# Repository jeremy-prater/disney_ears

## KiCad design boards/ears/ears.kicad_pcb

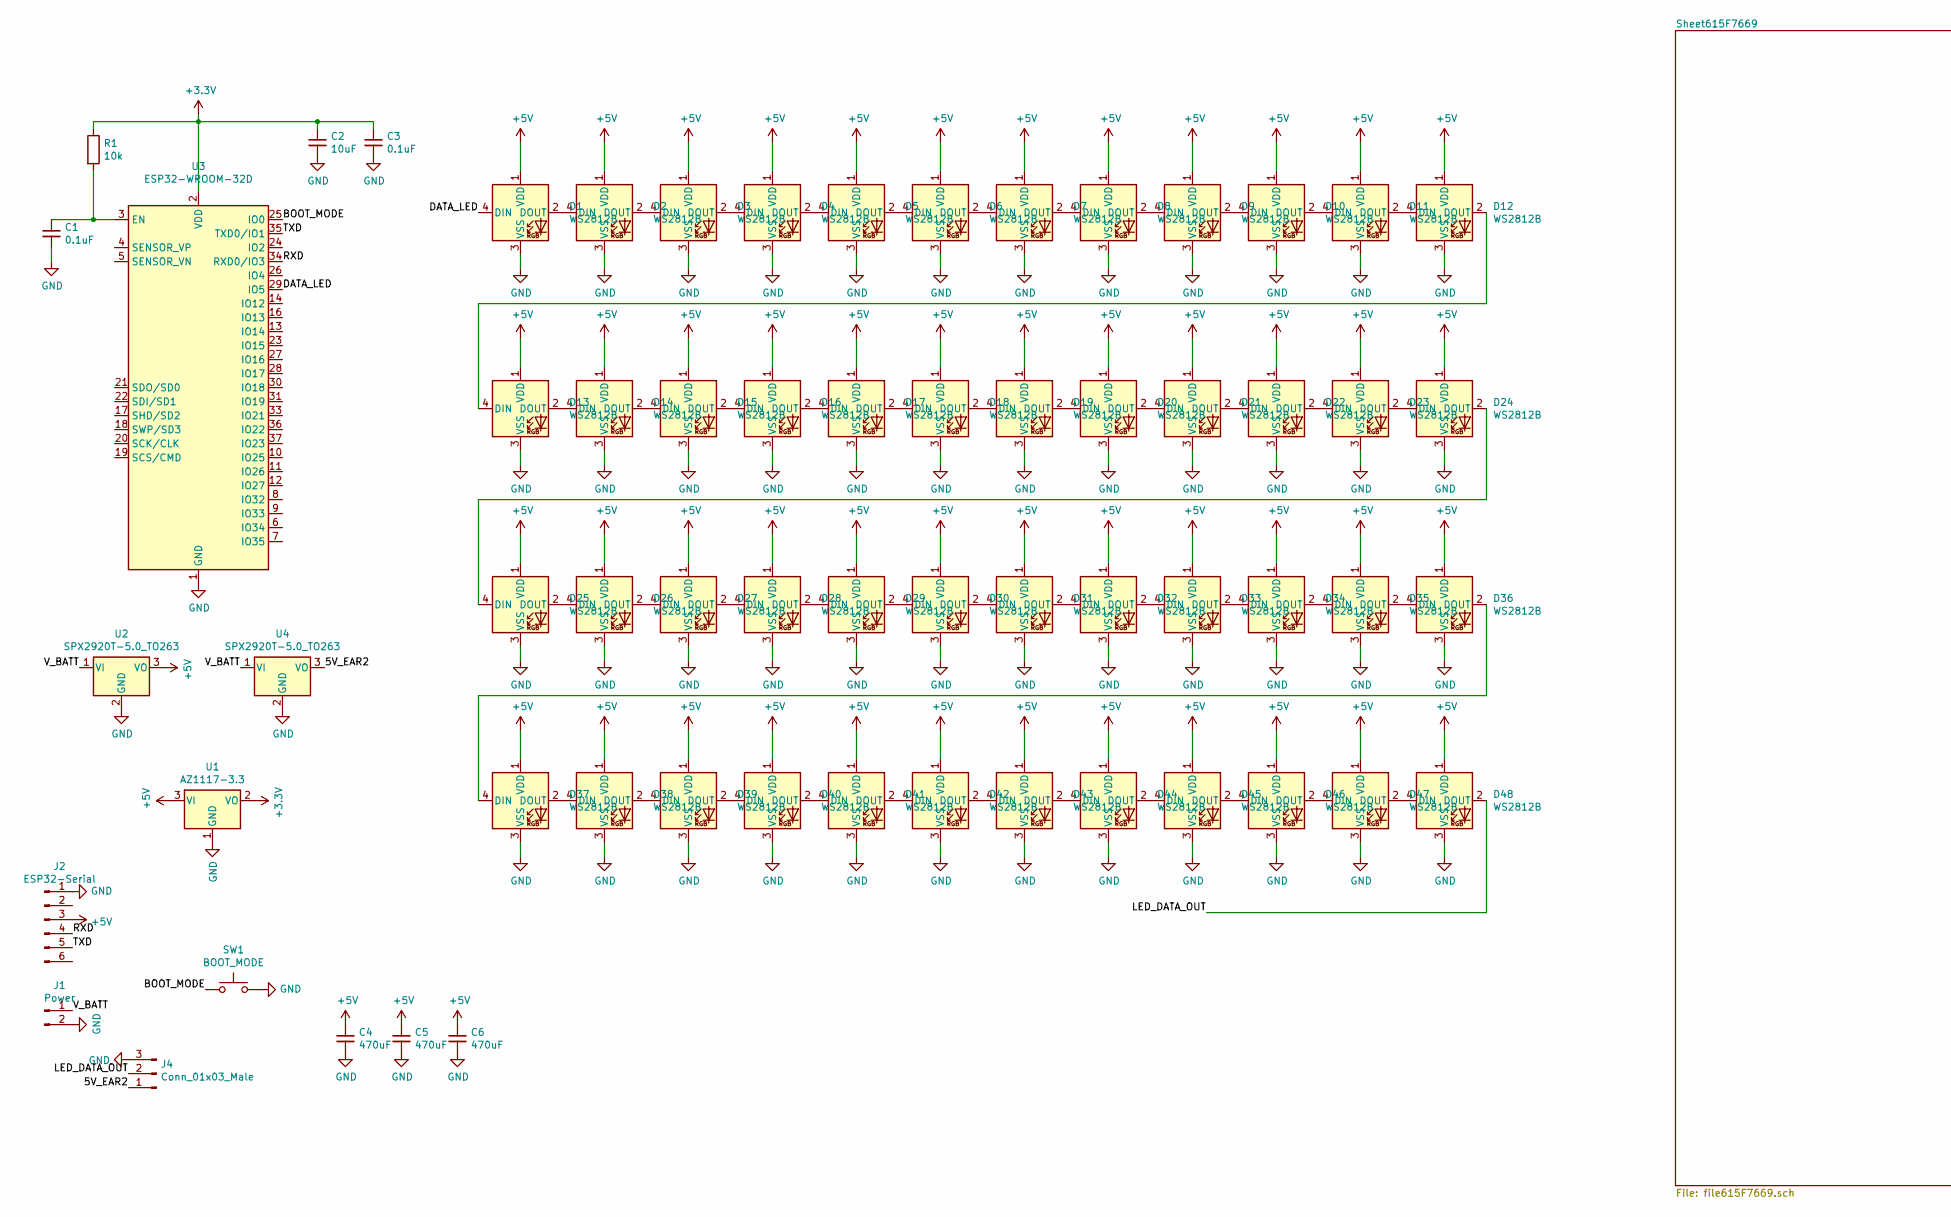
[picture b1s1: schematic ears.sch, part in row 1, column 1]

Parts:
C1, C3: 0.1uF; C_0504_1310Metric_Pad0.83x1.28mm_HandSolder
C2: 10uF; C_0504_1310Metric_Pad0.83x1.28mm_HandSolder
C4, C5, C6: 470uF; CP_EIA-7343-15_Kemet-W_Pad2.25x2.55mm_HandSolder
D1, D2, D3, D4, D5, D6, D7, D8, D9, D10, D11, D12, D13, D14, D15, D16, D17, D18, D19, D20, D21, D22, D23, D24, D25, D26, D27, D28, D29, D30, D31, D32, D33, D34, D35, D36, D37, D38, D39, D40, D41, D42, D43, D44, D45, D46, D47, D48: WS2812B; LED_WS2812B_PLCC4_5.0x5.0mm_P3.2mm
J1: Power; PinHeader_1x02_P1.00mm_Horizontal
J2: ESP32-Serial; PinHeader_1x06_P1.00mm_Horizontal
J4: Conn_01x03_Male; PinHeader_1x03_P1.00mm_Horizontal
R1: 10k; R_0603_1608Metric_Pad0.98x0.95mm_HandSolder
SW1: BOOT_MODE; SW_SPST_TL3342
U1: AZ1117-3.3; SOT-223
U2, U4: SPX2920T-5.0_TO263; TO-263-3_TabPin2
U3: ESP32-WROOM-32D; ESP32-WROOM-32

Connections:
+3V3: C2.1, C3.1, R1.1, U1.2 (VO), U3.2 (VDD)
+5V: C4.1, C5.1, C6.1, D1.1 (VDD), D2.1 (VDD), D3.1 (VDD), D4.1 (VDD), D5.1 (VDD), D6.1 (VDD), D7.1 (VDD), D8.1 (VDD), D9.1 (VDD), D10.1 (VDD), D11.1 (VDD), D12.1 (VDD), D13.1 (VDD), D14.1 (VDD), D15.1 (VDD), D16.1 (VDD), D17.1 (VDD), D18.1 (VDD), D19.1 (VDD), D20.1 (VDD), D21.1 (VDD), D22.1 (VDD), D23.1 (VDD), D24.1 (VDD), D25.1 (VDD), D26.1 (VDD), D27.1 (VDD), D28.1 (VDD), D29.1 (VDD), D30.1 (VDD), D31.1 (VDD), D32.1 (VDD), D33.1 (VDD), D34.1 (VDD), D35.1 (VDD), D36.1 (VDD), D37.1 (VDD), D38.1 (VDD), D39.1 (VDD), D40.1 (VDD), D41.1 (VDD), D42.1 (VDD), D43.1 (VDD), D44.1 (VDD), D45.1 (VDD), D46.1 (VDD), D47.1 (VDD), D48.1 (VDD), J2.3, U1.3 (VI), U2.3 (VO)
/5V_EAR2: J4.1, U4.3 (VO)
/BOOT_MODE: SW1.1, U3.25 (IO0)
/DATA_LED: D1.4 (DIN), U3.29 (IO5)
/LED_DATA_OUT: D48.2 (DOUT), J4.2
/RXD: J2.4, U3.34 (RXD0/IO3)
/TXD: J2.5, U3.35 (TXD0/IO1)
/V_BATT: J1.1, U2.1 (VI), U4.1 (VI)
GND: C1.2, C2.2, C3.2, C4.2, C5.2, C6.2, D1.3 (VSS), D2.3 (VSS), D3.3 (VSS), D4.3 (VSS), D5.3 (VSS), D6.3 (VSS), D7.3 (VSS), D8.3 (VSS), D9.3 (VSS), D10.3 (VSS), D11.3 (VSS), D12.3 (VSS), D13.3 (VSS), D14.3 (VSS), D15.3 (VSS), D16.3 (VSS), D17.3 (VSS), D18.3 (VSS), D19.3 (VSS), D20.3 (VSS), D21.3 (VSS), D22.3 (VSS), D23.3 (VSS), D24.3 (VSS), D25.3 (VSS), D26.3 (VSS), D27.3 (VSS), D28.3 (VSS), D29.3 (VSS), D30.3 (VSS), D31.3 (VSS), D32.3 (VSS), D33.3 (VSS), D34.3 (VSS), D35.3 (VSS), D36.3 (VSS), D37.3 (VSS), D38.3 (VSS), D39.3 (VSS), D40.3 (VSS), D41.3 (VSS), D42.3 (VSS), D43.3 (VSS), D44.3 (VSS), D45.3 (VSS), D46.3 (VSS), D47.3 (VSS), D48.3 (VSS), J1.2, J2.1, J4.3, SW1.2, U1.1 (GND), U2.2 (GND), U3.1 (GND), U3.15 (GND), U3.38 (GND), U3.39 (GND), U4.2 (GND)
unnamed: C1.1, R1.2, U3.3 (EN)
unnamed: D1.2 (DOUT), D2.4 (DIN)
unnamed: D2.2 (DOUT), D3.4 (DIN)
unnamed: D3.2 (DOUT), D4.4 (DIN)
unnamed: D4.2 (DOUT), D5.4 (DIN)
unnamed: D5.2 (DOUT), D6.4 (DIN)
unnamed: D6.2 (DOUT), D7.4 (DIN)
unnamed: D7.2 (DOUT), D8.4 (DIN)
unnamed: D8.2 (DOUT), D9.4 (DIN)
unnamed: D10.2 (DOUT), D11.4 (DIN)
unnamed: D9.2 (DOUT), D10.4 (DIN)
unnamed: D11.2 (DOUT), D12.4 (DIN)
unnamed: D12.2 (DOUT), D13.4 (DIN)
unnamed: D13.2 (DOUT), D14.4 (DIN)
unnamed: D14.2 (DOUT), D15.4 (DIN)
unnamed: D15.2 (DOUT), D16.4 (DIN)
unnamed: D16.2 (DOUT), D17.4 (DIN)
unnamed: D17.2 (DOUT), D18.4 (DIN)
unnamed: D18.2 (DOUT), D19.4 (DIN)
unnamed: D19.2 (DOUT), D20.4 (DIN)
unnamed: D20.2 (DOUT), D21.4 (DIN)
unnamed: D21.2 (DOUT), D22.4 (DIN)
unnamed: D22.2 (DOUT), D23.4 (DIN)
unnamed: D23.2 (DOUT), D24.4 (DIN)
unnamed: D24.2 (DOUT), D25.4 (DIN)
unnamed: D25.2 (DOUT), D26.4 (DIN)
unnamed: D26.2 (DOUT), D27.4 (DIN)
unnamed: D27.2 (DOUT), D28.4 (DIN)
unnamed: D28.2 (DOUT), D29.4 (DIN)
unnamed: D29.2 (DOUT), D30.4 (DIN)
unnamed: D30.2 (DOUT), D31.4 (DIN)
unnamed: D31.2 (DOUT), D32.4 (DIN)
unnamed: D32.2 (DOUT), D33.4 (DIN)
unnamed: D33.2 (DOUT), D34.4 (DIN)
unnamed: D34.2 (DOUT), D35.4 (DIN)
unnamed: D35.2 (DOUT), D36.4 (DIN)
unnamed: D36.2 (DOUT), D37.4 (DIN)
unnamed: D37.2 (DOUT), D38.4 (DIN)
unnamed: D38.2 (DOUT), D39.4 (DIN)
unnamed: D39.2 (DOUT), D40.4 (DIN)
unnamed: D40.2 (DOUT), D41.4 (DIN)
unnamed: D41.2 (DOUT), D42.4 (DIN)
unnamed: D42.2 (DOUT), D43.4 (DIN)
unnamed: D43.2 (DOUT), D44.4 (DIN)
unnamed: D44.2 (DOUT), D45.4 (DIN)
unnamed: D45.2 (DOUT), D46.4 (DIN)
unnamed: D46.2 (DOUT), D47.4 (DIN)
unnamed: D47.2 (DOUT), D48.4 (DIN)

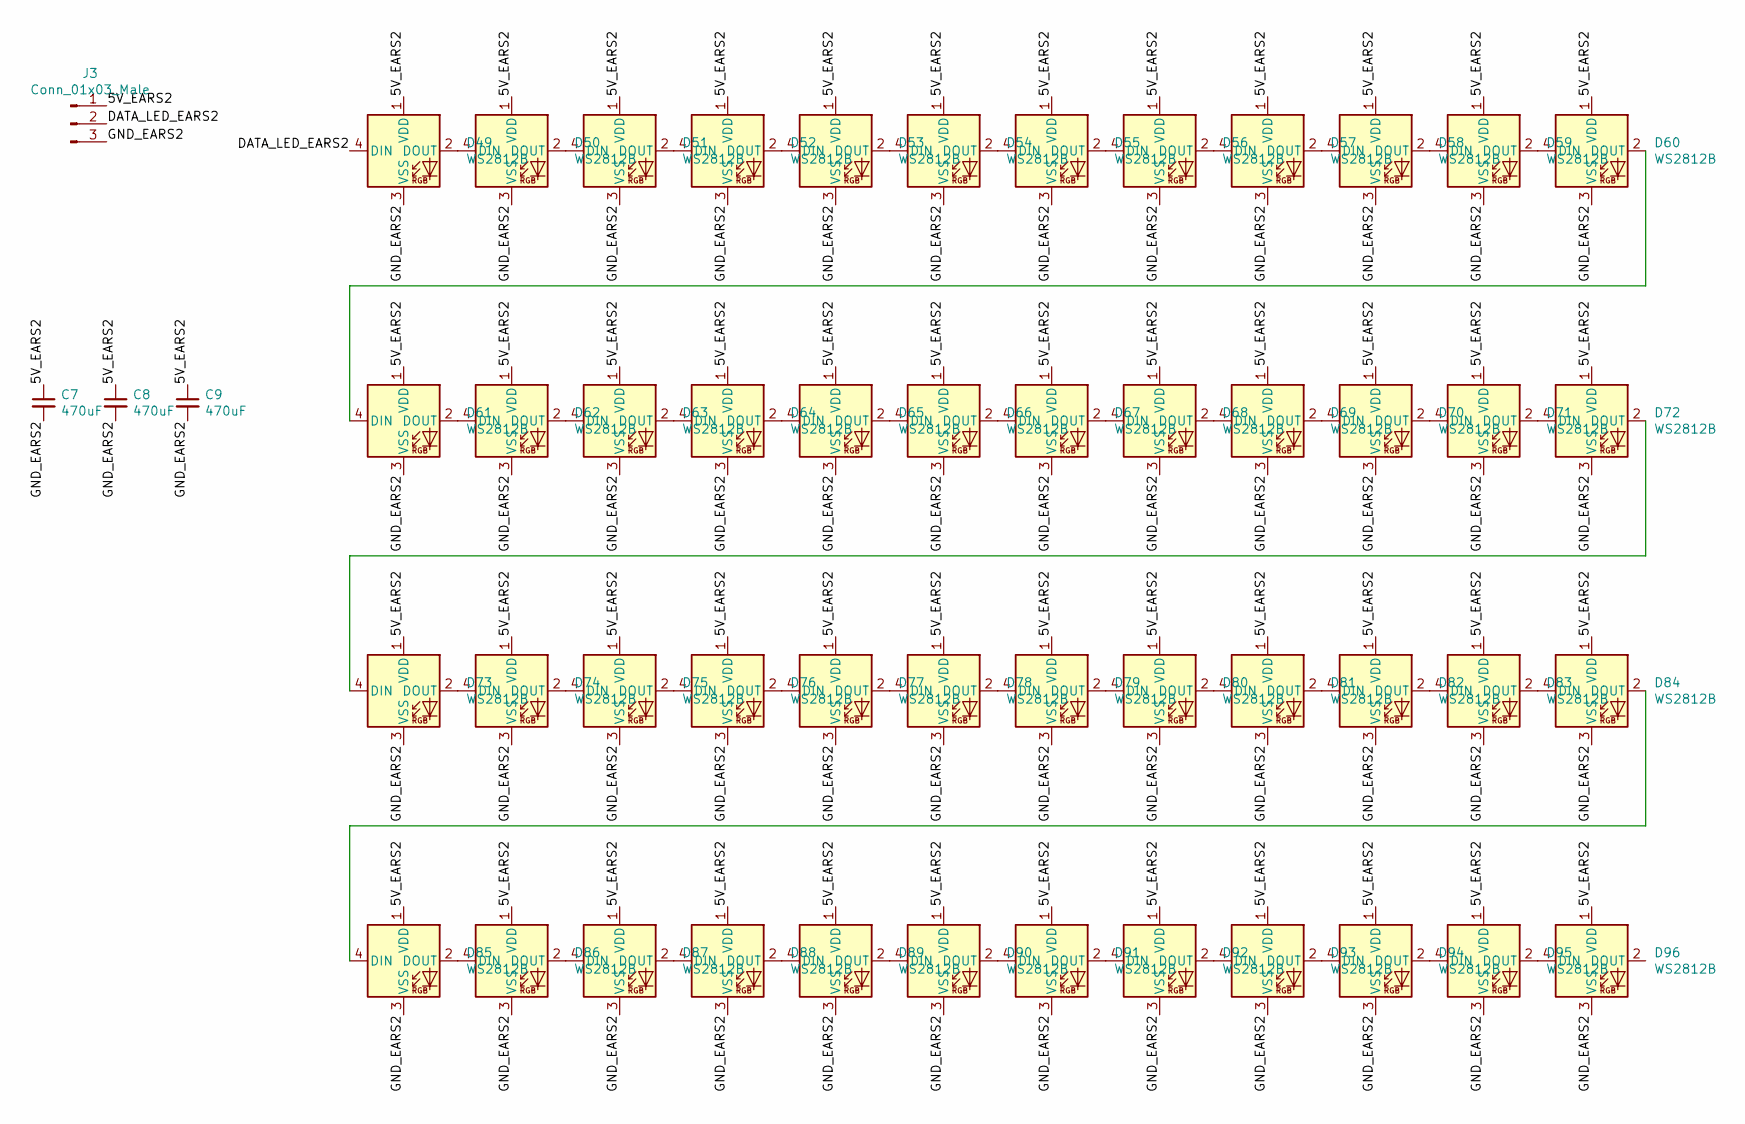
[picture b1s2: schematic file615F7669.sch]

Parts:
C7, C8, C9: 470uF; CP_EIA-7343-15_Kemet-W_Pad2.25x2.55mm_HandSolder
D49, D50, D51, D52, D53, D54, D55, D56, D57, D58, D59, D60, D61, D62, D63, D64, D65, D66, D67, D68, D69, D70, D71, D72, D73, D74, D75, D76, D77, D78, D79, D80, D81, D82, D83, D84, D85, D86, D87, D88, D89, D90, D91, D92, D93, D94, D95, D96: WS2812B; LED_WS2812B_PLCC4_5.0x5.0mm_P3.2mm
J3: Conn_01x03_Male; PinHeader_1x03_P1.00mm_Horizontal

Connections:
/Sheet615F7669/5V_EARS2: C7.1, C8.1, C9.1, D49.1 (VDD), D50.1 (VDD), D51.1 (VDD), D52.1 (VDD), D53.1 (VDD), D54.1 (VDD), D55.1 (VDD), D56.1 (VDD), D57.1 (VDD), D58.1 (VDD), D59.1 (VDD), D60.1 (VDD), D61.1 (VDD), D62.1 (VDD), D63.1 (VDD), D64.1 (VDD), D65.1 (VDD), D66.1 (VDD), D67.1 (VDD), D68.1 (VDD), D69.1 (VDD), D70.1 (VDD), D71.1 (VDD), D72.1 (VDD), D73.1 (VDD), D74.1 (VDD), D75.1 (VDD), D76.1 (VDD), D77.1 (VDD), D78.1 (VDD), D79.1 (VDD), D80.1 (VDD), D81.1 (VDD), D82.1 (VDD), D83.1 (VDD), D84.1 (VDD), D85.1 (VDD), D86.1 (VDD), D87.1 (VDD), D88.1 (VDD), D89.1 (VDD), D90.1 (VDD), D91.1 (VDD), D92.1 (VDD), D93.1 (VDD), D94.1 (VDD), D95.1 (VDD), D96.1 (VDD), J3.1
/Sheet615F7669/DATA_LED_EARS2: D49.4 (DIN), J3.2
/Sheet615F7669/GND_EARS2: C7.2, C8.2, C9.2, D49.3 (VSS), D50.3 (VSS), D51.3 (VSS), D52.3 (VSS), D53.3 (VSS), D54.3 (VSS), D55.3 (VSS), D56.3 (VSS), D57.3 (VSS), D58.3 (VSS), D59.3 (VSS), D60.3 (VSS), D61.3 (VSS), D62.3 (VSS), D63.3 (VSS), D64.3 (VSS), D65.3 (VSS), D66.3 (VSS), D67.3 (VSS), D68.3 (VSS), D69.3 (VSS), D70.3 (VSS), D71.3 (VSS), D72.3 (VSS), D73.3 (VSS), D74.3 (VSS), D75.3 (VSS), D76.3 (VSS), D77.3 (VSS), D78.3 (VSS), D79.3 (VSS), D80.3 (VSS), D81.3 (VSS), D82.3 (VSS), D83.3 (VSS), D84.3 (VSS), D85.3 (VSS), D86.3 (VSS), D87.3 (VSS), D88.3 (VSS), D89.3 (VSS), D90.3 (VSS), D91.3 (VSS), D92.3 (VSS), D93.3 (VSS), D94.3 (VSS), D95.3 (VSS), D96.3 (VSS), J3.3
unnamed: D49.2 (DOUT), D50.4 (DIN)
unnamed: D50.2 (DOUT), D51.4 (DIN)
unnamed: D51.2 (DOUT), D52.4 (DIN)
unnamed: D52.2 (DOUT), D53.4 (DIN)
unnamed: D53.2 (DOUT), D54.4 (DIN)
unnamed: D54.2 (DOUT), D55.4 (DIN)
unnamed: D55.2 (DOUT), D56.4 (DIN)
unnamed: D56.2 (DOUT), D57.4 (DIN)
unnamed: D57.2 (DOUT), D58.4 (DIN)
unnamed: D58.2 (DOUT), D59.4 (DIN)
unnamed: D59.2 (DOUT), D60.4 (DIN)
unnamed: D60.2 (DOUT), D61.4 (DIN)
unnamed: D61.2 (DOUT), D62.4 (DIN)
unnamed: D62.2 (DOUT), D63.4 (DIN)
unnamed: D63.2 (DOUT), D64.4 (DIN)
unnamed: D64.2 (DOUT), D65.4 (DIN)
unnamed: D65.2 (DOUT), D66.4 (DIN)
unnamed: D66.2 (DOUT), D67.4 (DIN)
unnamed: D67.2 (DOUT), D68.4 (DIN)
unnamed: D68.2 (DOUT), D69.4 (DIN)
unnamed: D69.2 (DOUT), D70.4 (DIN)
unnamed: D70.2 (DOUT), D71.4 (DIN)
unnamed: D71.2 (DOUT), D72.4 (DIN)
unnamed: D72.2 (DOUT), D73.4 (DIN)
unnamed: D73.2 (DOUT), D74.4 (DIN)
unnamed: D74.2 (DOUT), D75.4 (DIN)
unnamed: D75.2 (DOUT), D76.4 (DIN)
unnamed: D76.2 (DOUT), D77.4 (DIN)
unnamed: D77.2 (DOUT), D78.4 (DIN)
unnamed: D78.2 (DOUT), D79.4 (DIN)
unnamed: D79.2 (DOUT), D80.4 (DIN)
unnamed: D80.2 (DOUT), D81.4 (DIN)
unnamed: D81.2 (DOUT), D82.4 (DIN)
unnamed: D82.2 (DOUT), D83.4 (DIN)
unnamed: D83.2 (DOUT), D84.4 (DIN)
unnamed: D84.2 (DOUT), D85.4 (DIN)
unnamed: D85.2 (DOUT), D86.4 (DIN)
unnamed: D86.2 (DOUT), D87.4 (DIN)
unnamed: D87.2 (DOUT), D88.4 (DIN)
unnamed: D88.2 (DOUT), D89.4 (DIN)
unnamed: D89.2 (DOUT), D90.4 (DIN)
unnamed: D90.2 (DOUT), D91.4 (DIN)
unnamed: D91.2 (DOUT), D92.4 (DIN)
unnamed: D92.2 (DOUT), D93.4 (DIN)
unnamed: D93.2 (DOUT), D94.4 (DIN)
unnamed: D94.2 (DOUT), D95.4 (DIN)
unnamed: D95.2 (DOUT), D96.4 (DIN)

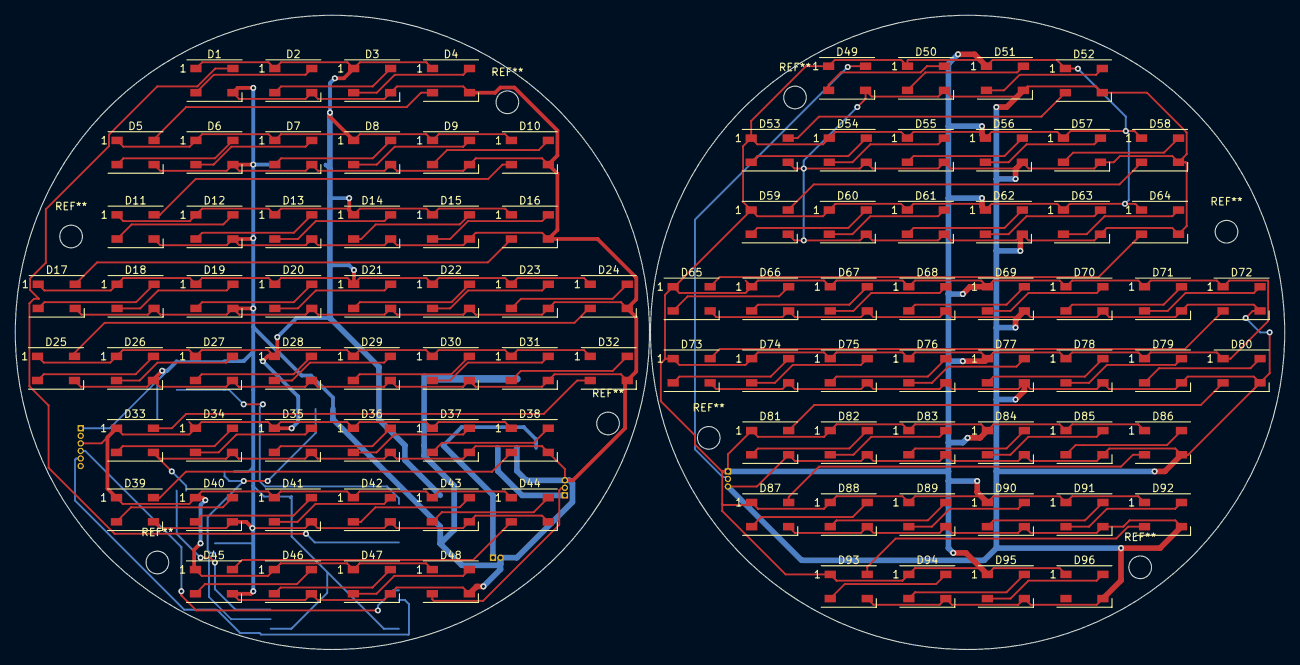
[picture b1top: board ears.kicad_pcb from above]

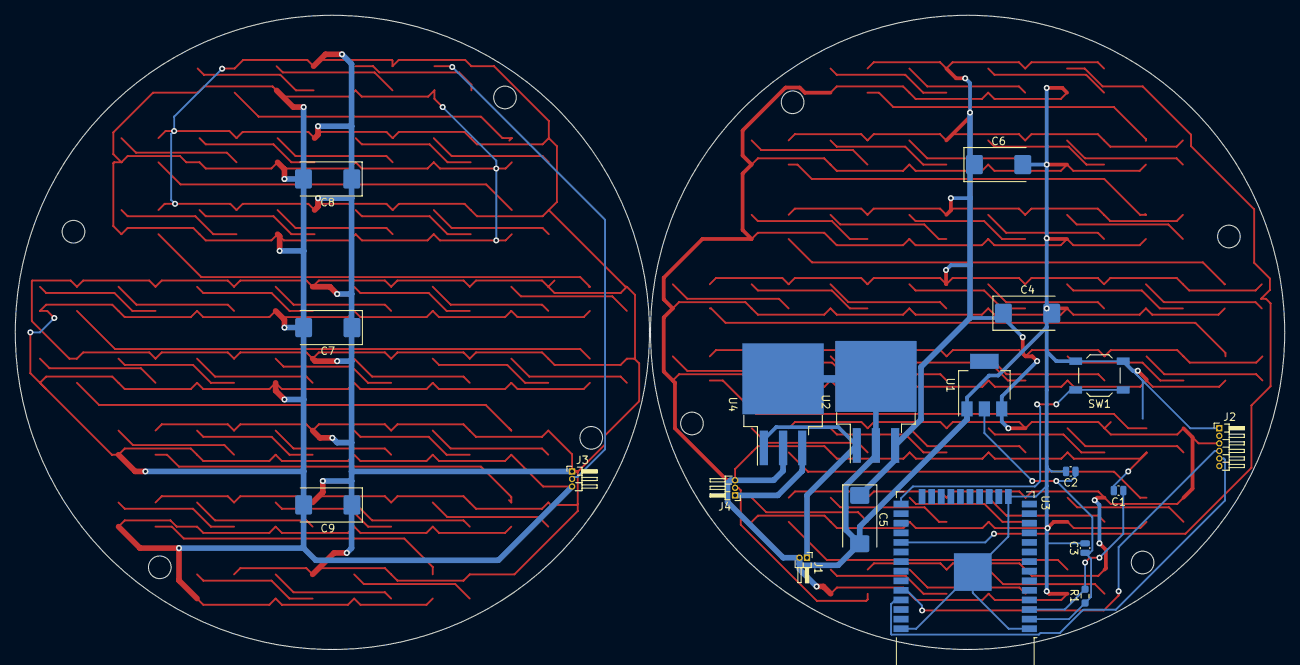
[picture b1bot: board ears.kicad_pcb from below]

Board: 2 copper layers, 168.1 x 84.0 mm, 115 parts (19 on the bottom side), 108 nets.

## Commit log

2021-08-29 - Add hello_world test project
2021-09-01 - Initial app commit
2021-09-03 - BLE Scan works!
2021-09-05 - Ears work
2021-09-10 - App + Board work
2021-09-11 - Ear boards V1
2021-09-11 - Final board work
2021-09-15 - UI circle
2021-09-16 - More ear UI work
2021-09-17 - UI work
2021-09-21 - LEDS and BLE work!!
2021-09-22 - Ear controller firmware
2021-09-23 - App work
2021-09-23 - LED view model
2021-09-23 - Disney ears work
2021-09-23 - Bitmap ears
2021-09-27 - End of trip
2022-01-05 - Emoji support for ears
2022-01-06 - Recycler emoji
2022-01-06 - Brightness tweaks
